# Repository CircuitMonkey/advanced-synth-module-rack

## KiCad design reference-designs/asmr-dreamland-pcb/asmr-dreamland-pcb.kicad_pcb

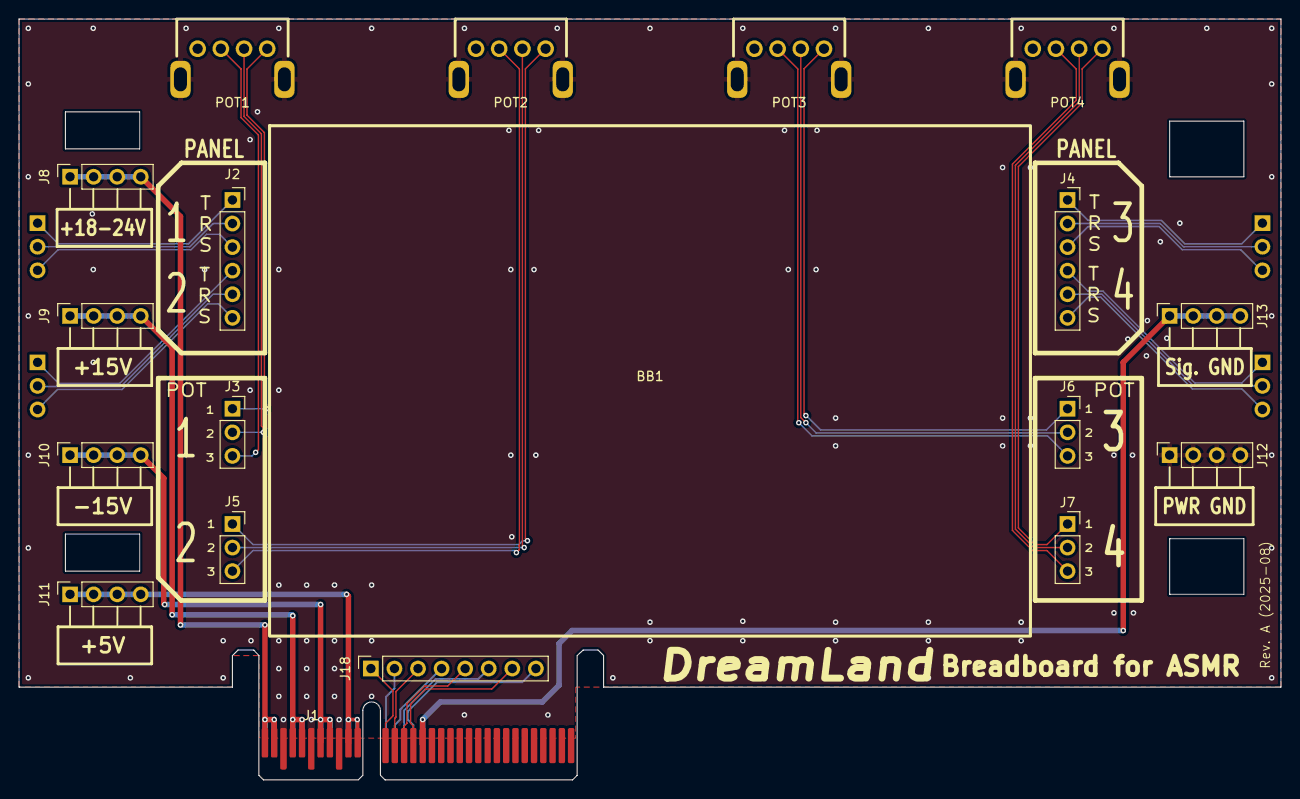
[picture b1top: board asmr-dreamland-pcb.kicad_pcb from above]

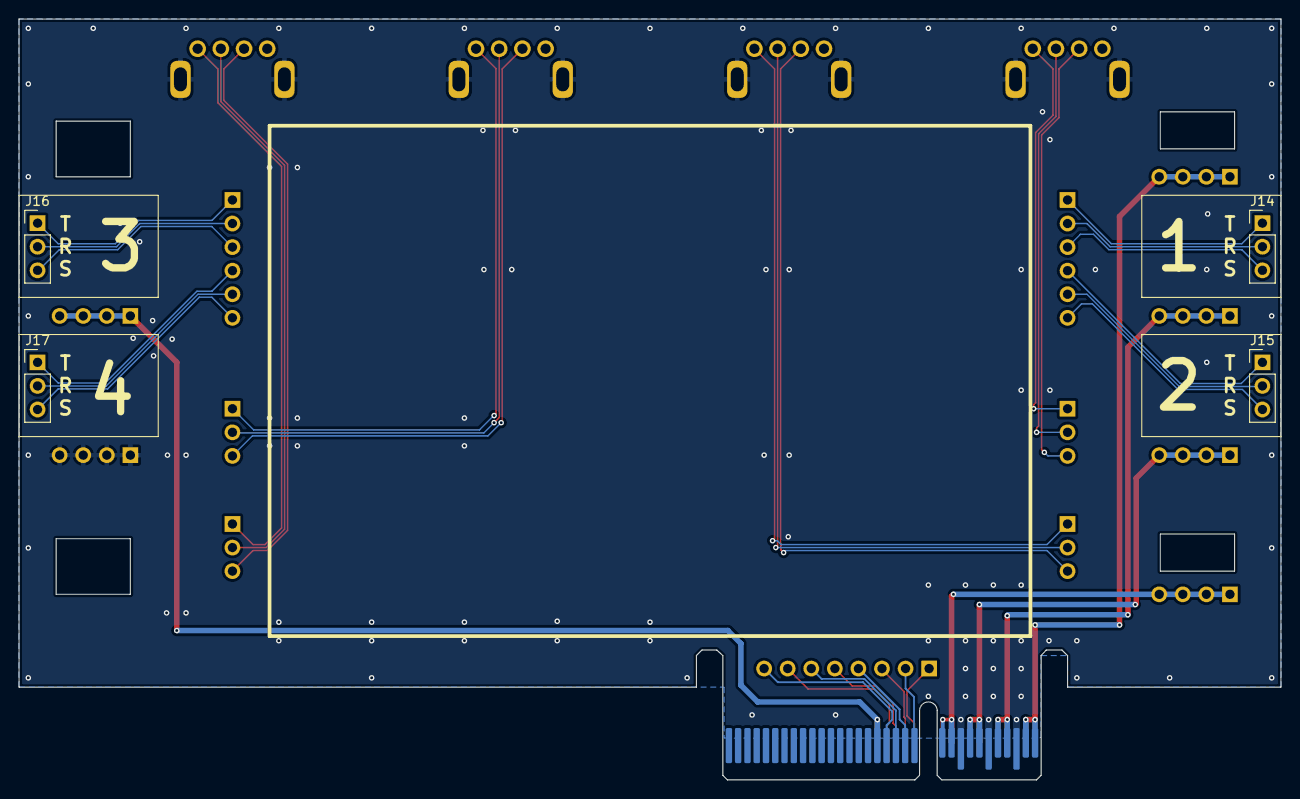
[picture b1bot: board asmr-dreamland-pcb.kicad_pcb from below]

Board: 2 copper layers, 136.0 x 82.0 mm, 23 parts (4 on the bottom side), 38 nets.

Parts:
BB1: Breadboard; breadboard-84x55
J1: ASMR-Edge-64
J2, J4: Conn_01x06; PinSocket_1x06_P2.54mm_Vertical
J3, J5, J6, J7: Conn_01x03; PinSocket_1x03_P2.54mm_Vertical
J8, J9, J10, J11, J12, J13: Conn_01x10; PinSocket_1x04_P2.54mm_Vertical
J14, J15, J16, J17: Conn_01x03; PinHeader_1x03_P2.54mm_Vertical
J18: Conn_01x08; PinSocket_1x08_P2.54mm_Vertical
POT1, POT2, POT3, POT4: 10K Log; pot-thd-ra-11mm

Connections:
+5V: J1.A10 (+5V), J1.A11 (+5V), J1.B10 (+5V), J1.B11 (+5V), J11.1, J11.2, J11.3, J11.4
+15V: J1.A4 (+15V), J1.A5 (+15V), J1.B4 (+15V), J1.B5 (+15V), J9.1, J9.2, J9.3, J9.4
+18-24V: J1.A1 (+18-24V), J1.A2 (+18-24V), J1.B1 (+18-24V), J1.B2 (+18-24V), J8.1, J8.2, J8.3, J8.4
-15V: J1.A7 (-15V), J1.A8 (-15V), J1.B7 (-15V), J1.B8 (-15V), J10.1, J10.2, J10.3, J10.4
GNDS: J1.A16 (SGND), J1.B16 (SGND), J13.1, J13.2, J13.3, J13.4
GND_CH: J1.A3 (GND), J1.A6 (GND), J1.A9 (GND), J1.B3 (GND), J1.B6 (GND), J1.B9 (GND), J12.1, J12.2, J12.3, J12.4, POT1.MP (MountPin), POT2.MP (MountPin), POT3.MP (MountPin), POT4.MP (MountPin)
unnamed: J1.A15 (CV), J18.8
unnamed: J1.A13 (ComA-SCK), J18.4
unnamed: J1.B13 (ComA-SDA), J18.3
unnamed: J1.A14 (ComB-SCK), J18.6
unnamed: J1.B14 (ComB-SDA), J18.5
unnamed: J1.B15 (Gate), J18.7
unnamed: J1.B12 (MIDI_IN), J18.1
unnamed: J1.A12 (Slot), J18.2
unnamed: J3.1, POT1.1
unnamed: J3.2, POT1.2
unnamed: J3.3, POT1.3
unnamed: J5.1, POT2.1
unnamed: J5.2, POT2.2
unnamed: J5.3, POT2.3
unnamed: J6.1, POT3.1
unnamed: J6.2, POT3.2
unnamed: J6.3, POT3.3
unnamed: J7.1, POT4.1
unnamed: J7.2, POT4.2
unnamed: J7.3, POT4.3
unnamed: J2.1, J14.1
unnamed: J2.2, J14.2
unnamed: J2.3, J14.3
unnamed: J2.4, J15.1
unnamed: J2.5, J15.2
unnamed: J2.6, J15.3
unnamed: J4.1, J16.1
unnamed: J4.2, J16.2
unnamed: J4.3, J16.3
unnamed: J4.4, J17.1
unnamed: J4.5, J17.2
unnamed: J4.6, J17.3
